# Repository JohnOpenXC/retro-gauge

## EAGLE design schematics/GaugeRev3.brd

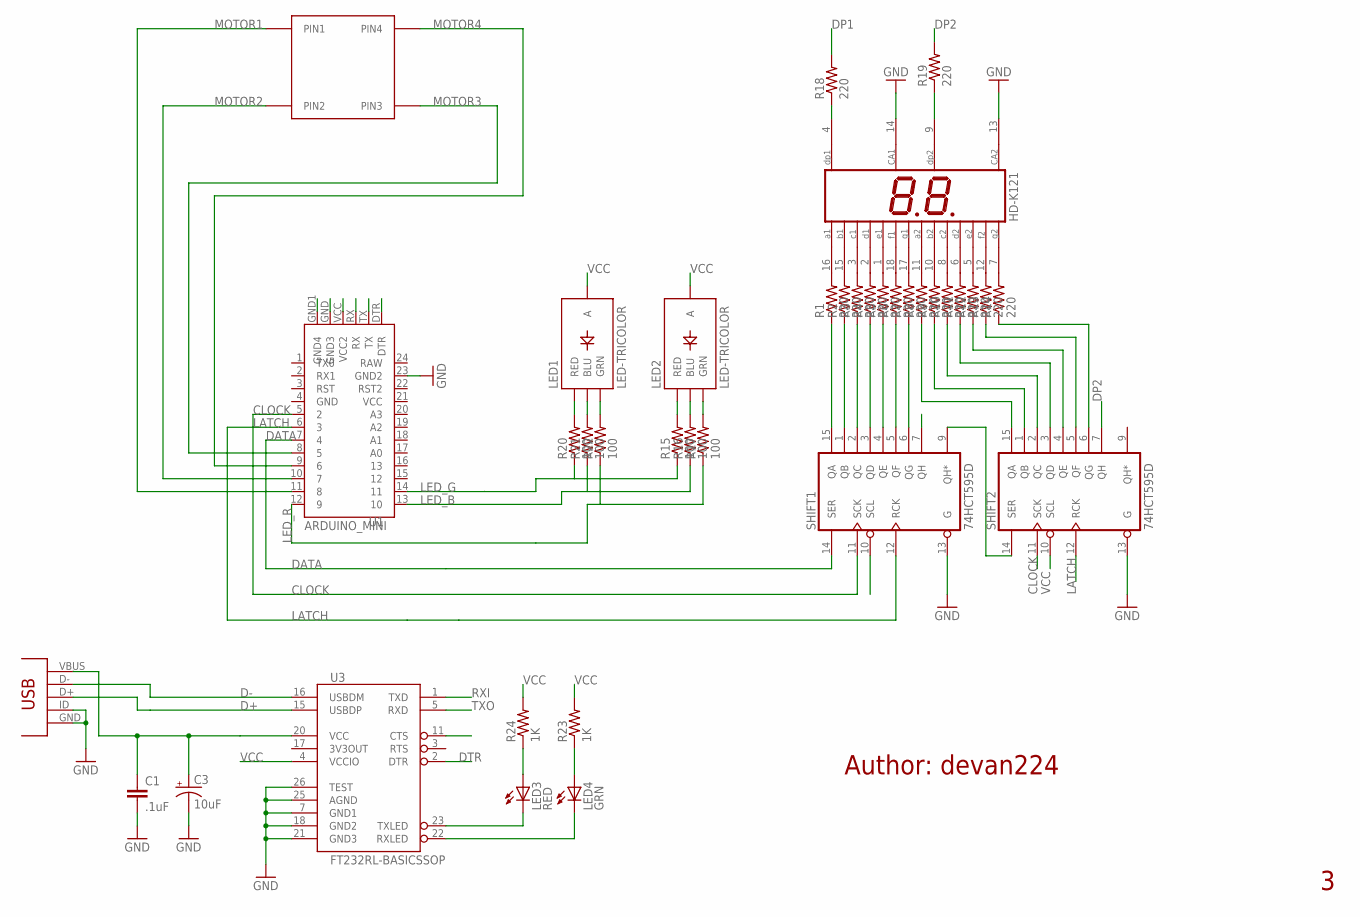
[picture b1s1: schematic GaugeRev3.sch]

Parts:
C1: .1uF; 1210
C3: 10uF; EIA3216-KIT
DIS2: HD-K121; HDSP-R
LED1, LED2: LED-TRICOLOR; LED-TRICOLOR-SMD
LED3: RED; LED-1206
LED4: GRN; LED-1206
R1, R2, R3, R4, R5, R6, R7, R8, R9, R10, R11, R12, R13, R14, R18, R19: 220; R1206
R15, R16, R17, R20, R21, R22: 100; R1206
R23, R24: 1K; 1206
SHIFT1, SHIFT2: 74HCT595D; SO16
U1: ARDUINO_MINI
U2: VID29
U3: FT232RL-BASICSSOP; SSOP28DB
U$1: USB-MINI-VERT

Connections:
1: DIS2.4 (DP1), R18.1
2: DIS2.9 (DP2), R19.1
A1: R1.1, SHIFT1.15 (QA)
A2: R8.1, SHIFT2.15 (QA)
B1: R2.1, SHIFT1.1 (QB)
B2: R9.1, SHIFT2.1 (QB)
C1: R3.1, SHIFT1.2 (QC)
CLOCK: SHIFT1.11 (SCK), SHIFT2.11 (SCK), U1.5 (2)
D1: R4.1, SHIFT1.3 (QD)
D+: U3.15 (USBDP), U$1.D+
D-: U3.16 (USBDM), U$1.D-
DATA: SHIFT1.14 (SER), U1.7 (4)
DP1: R18.2, SHIFT1.7 (QH)
DP2: R19.2, SHIFT2.7 (QH)
DTR: U1.DTR, U3.2 (DTR)
E1: R5.1, SHIFT1.4 (QE)
F1: R6.1, SHIFT1.5 (QF)
G1: R7.1, SHIFT1.6 (QG)
G2: R14.1, SHIFT2.6 (QG)
GND: C1.2, C3.C (-), DIS2.13 (CA2), DIS2.14 (CA1), SHIFT1.8 (GND), SHIFT1.13 (G), SHIFT2.8 (GND), SHIFT2.13 (G), U1.23 (GND2), U1.GND (GND3), U1.GND1 (GND4), U3.7 (GND1), U3.11 (CTS), U3.18 (GND2), U3.21 (GND3), U3.25 (AGND), U3.26 (TEST), U$1.GND, U$1.ID
LATCH: SHIFT1.12 (RCK), SHIFT2.12 (RCK), U1.6 (3)
LED_B: R16.1, R21.1, U1.13 (10)
LED_G: R15.1, R20.1, U1.14 (11)
LED_R: R17.1, R22.1, U1.12 (9)
MOTOR1: U1.11 (8), U2.PIN1
MOTOR2: U1.10 (7), U2.PIN2
MOTOR3: U1.8 (5), U2.PIN3
MOTOR4: U1.9 (6), U2.PIN4
unnamed: DIS2.16 (A1), R1.2
unnamed: DIS2.15 (B1), R2.2
unnamed: DIS2.3 (C1), R3.2
unnamed: DIS2.2 (D1), R4.2
unnamed: DIS2.1 (E1), R5.2
unnamed: DIS2.18 (F1), R6.2
unnamed: DIS2.17 (G1), R7.2
unnamed: DIS2.11 (A2), R8.2
unnamed: DIS2.10 (B2), R9.2
unnamed: DIS2.8 (C2), R10.2
unnamed: DIS2.6 (D2), R11.2
unnamed: DIS2.5 (E2), R12.2
unnamed: DIS2.12 (F2), R13.2
unnamed: DIS2.7 (G2), R14.2
unnamed: LED2.G (GRN), R17.2
unnamed: LED2.B (BLU), R16.2
unnamed: LED3.C, U3.23 (TXLED)
unnamed: LED4.C, U3.22 (RXLED)
unnamed: R10.1, SHIFT2.2 (QC)
unnamed: R11.1, SHIFT2.3 (QD)
unnamed: R12.1, SHIFT2.4 (QE)
unnamed: R13.1, SHIFT2.5 (QF)
unnamed: LED2.R (RED), R15.2
unnamed: LED1.G (GRN), R22.2
unnamed: LED1.B (BLU), R21.2
unnamed: LED1.R (RED), R20.2
unnamed: LED4.A, R23.1
unnamed: LED3.A, R24.1
Q*: SHIFT1.9 (QH*), SHIFT2.14 (SER)
RXI: U1.RX, U3.1 (TXD)
TXO: U1.TX, U3.5 (RXD)
VBUS: C1.1, C3.A (+), U3.20 (VCC), U$1.VBUS
VCC: LED1.A, LED2.A, R23.2, R24.2, SHIFT1.10 (SCL), SHIFT1.16 (VCC), SHIFT2.10 (SCL), SHIFT2.16 (VCC), U1.VCC (VCC2), U3.4 (VCCIO)

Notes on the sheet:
Author: devan224

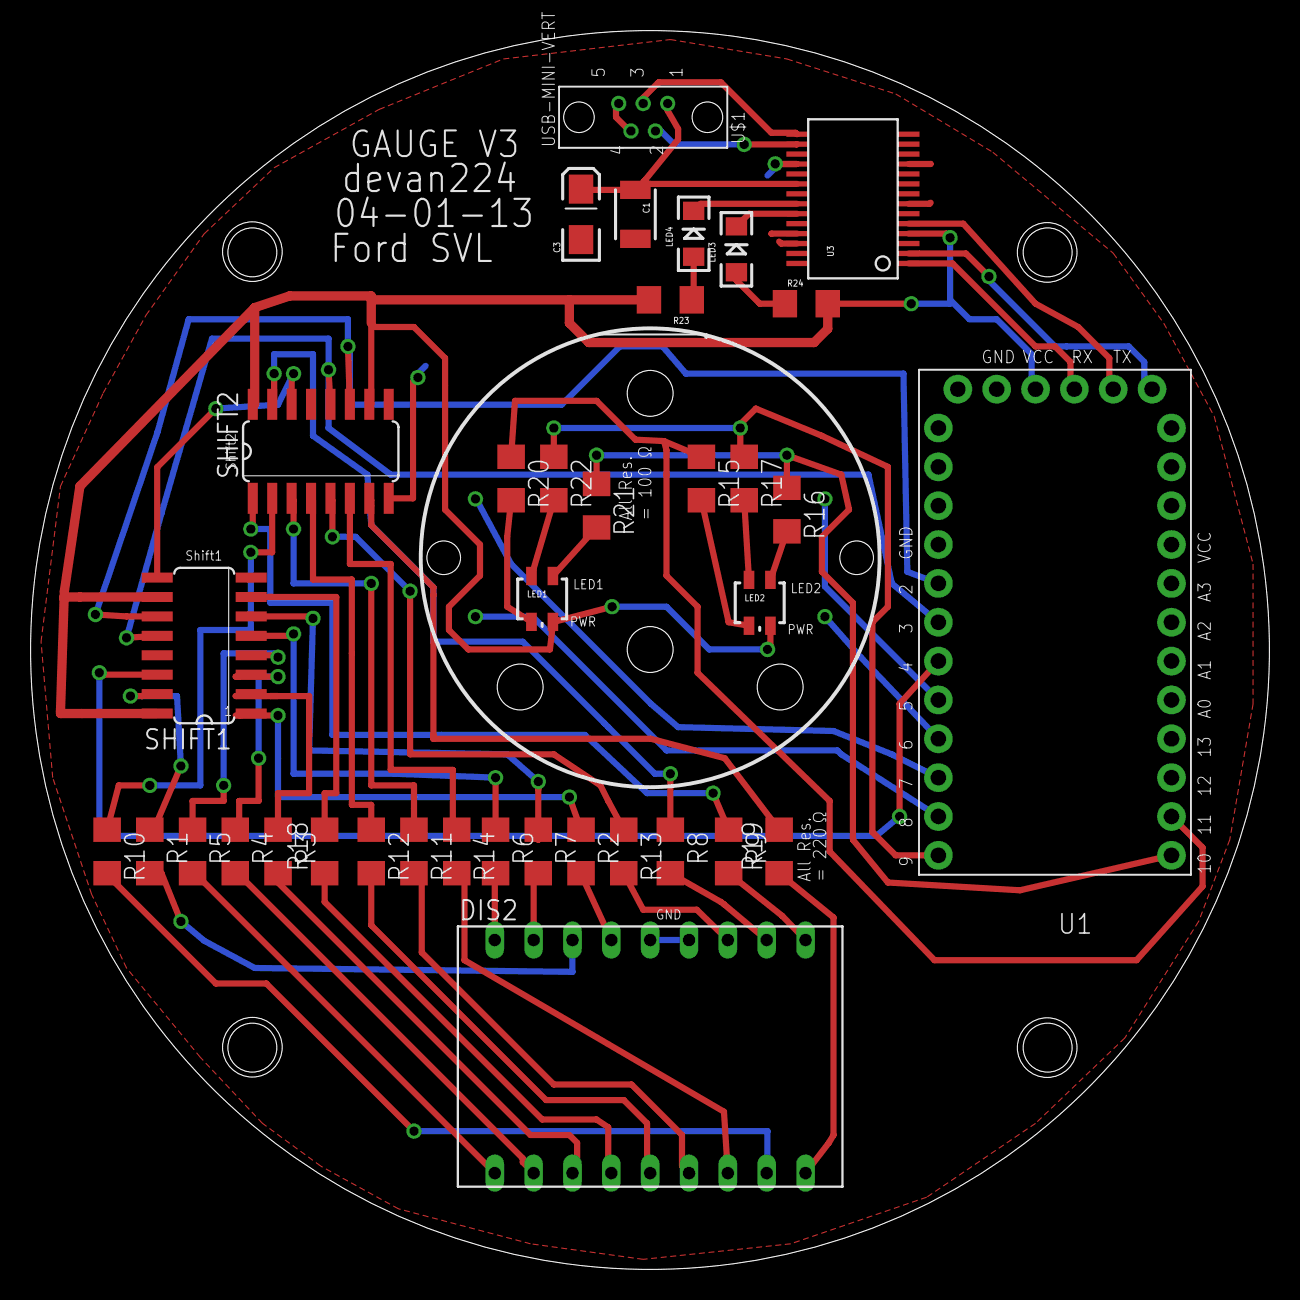
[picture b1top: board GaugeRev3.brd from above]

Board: 2 copper layers, 81.0 x 81.0 mm, 37 parts (0 on the bottom side), 61 nets.

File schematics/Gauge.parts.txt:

Partlist

Exported from GaugeRev2.sch at 4/1/13 6:07 PM

EAGLE Version 6.2.0 Copyright (c) 1988-2012 CadSoft

Assembly variant: 

Part     Value             Device            Package          Library   Sheet

C1       .1uF              CAP1210           1210             SparkFun  1
C3       10uF              CAP_POL1206-KIT   EIA3216-KIT      SparkFun  1
DIS2     HD-K121           HD-K121           HDSP-R           HDSP-523E 1
LED1     LED-TRICOLOR      LED-TRICOLOR      LED-TRICOLOR-SMD SparkFun  1
LED2     LED-TRICOLOR      LED-TRICOLOR      LED-TRICOLOR-SMD SparkFun  1
LED3     RED               LED1206           LED-1206         SparkFun  1
LED4     GRN               LED1206           LED-1206         SparkFun  1
R1       220               R-US_R1206        R1206            resistor  1
R2       220               R-US_R1206        R1206            resistor  1
R3       220               R-US_R1206        R1206            resistor  1
R4       220               R-US_R1206        R1206            resistor  1
R5       220               R-US_R1206        R1206            resistor  1
R6       220               R-US_R1206        R1206            resistor  1
R7       220               R-US_R1206        R1206            resistor  1
R8       220               R-US_R1206        R1206            resistor  1
R9       220               R-US_R1206        R1206            resistor  1
R10      220               R-US_R1206        R1206            resistor  1
R11      220               R-US_R1206        R1206            resistor  1
R12      220               R-US_R1206        R1206            resistor  1
R13      220               R-US_R1206        R1206            resistor  1
R14      220               R-US_R1206        R1206            resistor  1
R15      100               R-US_R1206        R1206            resistor  1
R16      100               R-US_R1206        R1206            resistor  1
R17      100               R-US_R1206        R1206            resistor  1
R18      220               R-US_R1206        R1206            resistor  1
R19      220               R-US_R1206        R1206            resistor  1
R20      100               R-US_R1206        R1206            resistor  1
R21      100               R-US_R1206        R1206            resistor  1
R22      100               R-US_R1206        R1206            resistor  1
R23      1K                RESISTOR1206      1206             SparkFun  1
R24      1K                RESISTOR1206      1206             SparkFun  1
SHIFT1   74HCT595D         74HCT595D         SO16             74xx-eu   1
SHIFT2   74HCT595D         74HCT595D         SO16             74xx-eu   1
U$1      USB-MINI-VERT     USB-MINI-VERT     USB-MINI-VERT    Evans     1
U1       ARDUINO_MINI      ARDUINO_MINI      ARDUINO_MINI     SparkFun  1
U2       VID29             VID29             VID29            Evans     1
U3       FT232RL-BASICSSOP FT232RL-BASICSSOP SSOP28DB         SparkFun  1

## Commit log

2013-02-07 cleaned up 'nextUpdate' and timing issues
2013-02-08 Maybe fixed a divide by zero bug. (Untested.)
2013-02-08 Added some debugging data display
2013-02-08 Corrected the colors.
2013-02-08 Fixed the units on the MPG calculation.
2013-02-11 MPG now gathers half a second of data for each calculation.
2013-02-19 MPG using mean of last 500ms of fuel and odo data. (Not quite working yet.)
2013-02-27 Increased MPG smoothing to 1 second, reduced the chances of a smoothed result of zero.
2013-03-22 Changed the MPG smoothing to 2 seconds, removed the debug statements.
2013-04-01 added FTDI chip to board
2013-04-02 layout completed for V3
2013-04-17 updated schematics
2013-04-17 Updated BOM
2013-04-24 Changed the MPG smoothing from 2 seconds to 5. Also limiting the data to 99.

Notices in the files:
parts and their libraries:
SparkFun: Licensing: CC v3.0 Share-Alike You are welcome to use this library for commercial purposes.
